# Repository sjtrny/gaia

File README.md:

# gaia

Gaia is a custom built environment sensor. This repository contains:
- parts list
- required software and setup instructions

## Overview

Gaia provides the following data:
- Ambient Lux
- Local Temperature (near device)
- Local Humidity
- Local Pressure
- Local Gas Resistance (Air Quality)
- Remote Temperature (away from device)

Two I2C sensor are used to collect this data:
- VEML770 (ambient lux)
- BME680 (local readings)
- DS18B20 waterproof (remote temp)

Temperature and Humidity are displayed on an Adafruit LCD.

Gaia runs on [ESPHome](https://esphome.io). See `gaia.yml`  for the configuration of the device.

## AdaFruit RGB LCD Shield

ESPHome does not have an official component for the AdaFruit RB LCD Sheild so I have written a component
for it which you can find in the `custom_components`  folder.

## VEML7700 Support

ESPHome does not have an official component for the VEMl7700 device, so I have written a small device wrapper `veml7700.h`, which leverages the "Adafruit VEML7700 Library".

## Parts List

The parts list can be found in the `parts.xlsx` file.

## Hardware and Wiring

TODO

## Instructions

1. Create virtual environment and install dependencies

```
./setup.sh
```

2. Activate virtual environment

```
source venv/bin/activate
```

3. Add wifi details to  `gaia.yml`

4. Plug in ESP32 via USB

5. Compile and upload to ESP32

```
		esphome gaia.yml run
```

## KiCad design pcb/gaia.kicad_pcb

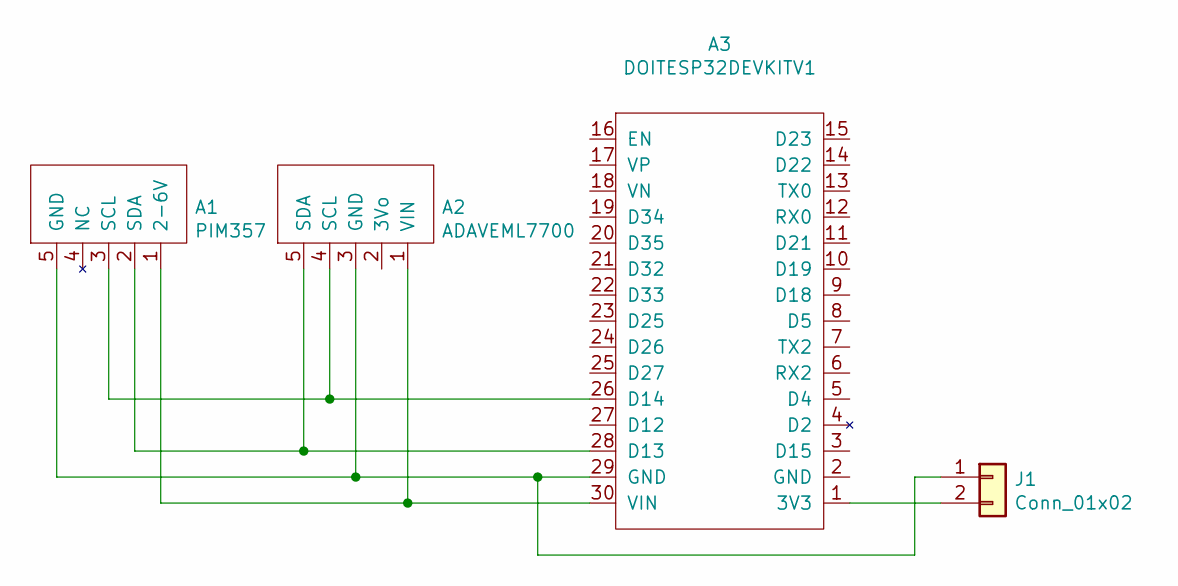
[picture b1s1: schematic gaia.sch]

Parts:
A1: PIM357
A2: ADAVEML7700
A3: DOITESP32DEVKITV1
J1: Conn_01x02; PinHeader_1x02_P2.54mm_Vertical

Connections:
unnamed: A1.1 (2-6V), A2.1 (VIN), A3.30 (VIN)
unnamed: A1.2 (SDA), A2.5 (SDA), A3.28 (D13)
unnamed: A1.3 (SCL), A2.4 (SCL), A3.26 (D14)
unnamed: A1.5 (GND), A2.3 (GND), A3.29 (GND), J1.1
unnamed: A3.1 (3V3), J1.2

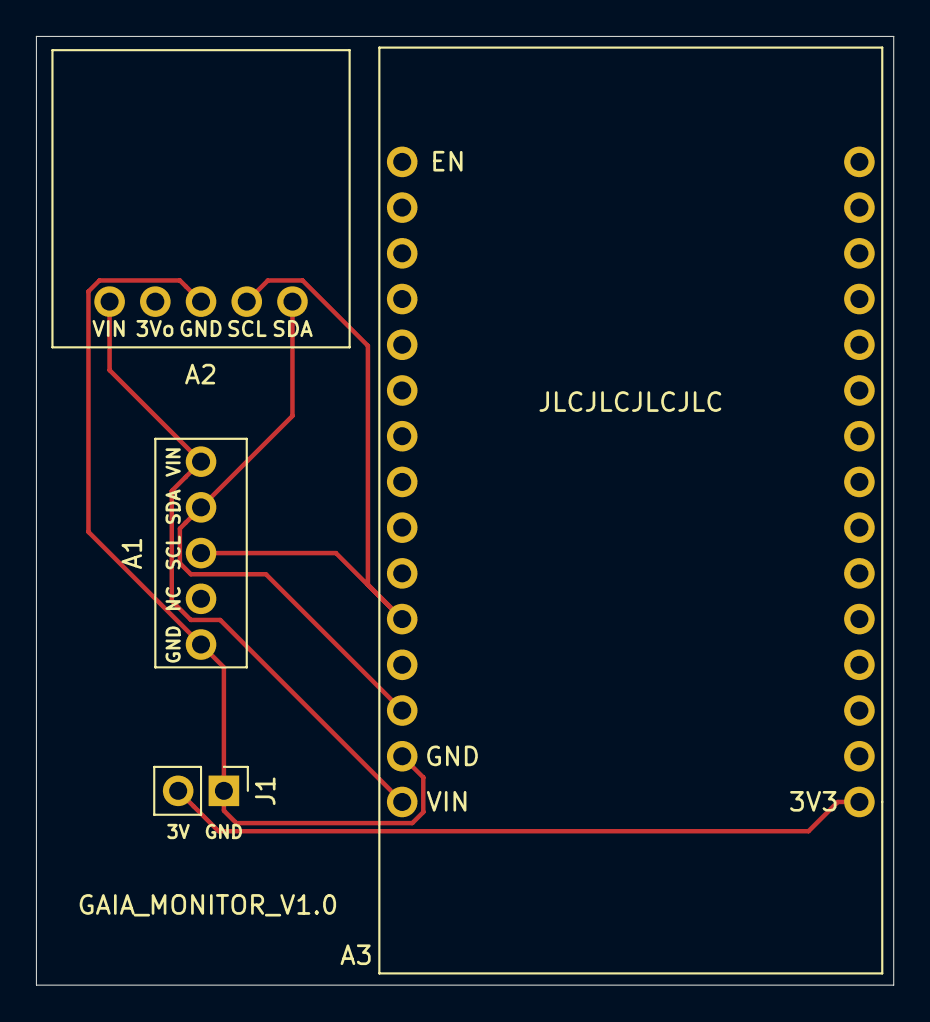
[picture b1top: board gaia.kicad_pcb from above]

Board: 2 copper layers, 47.6 x 52.7 mm, 4 parts (0 on the bottom side), 5 nets.

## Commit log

2020-01-06 Initial upload
2020-01-06 Made setup.sh executable (+x) and improved instructions
2020-01-06 Fixed bugs
2020-01-06 Improved instructions
2020-01-06 Removed dead command
2020-01-10 Migrated to ESPHome
2020-01-10 Removing files
2020-01-10 Added wifi instructions
2020-05-27 Added PCB, temp probe and LCD
2020-05-27 Restoring config file
